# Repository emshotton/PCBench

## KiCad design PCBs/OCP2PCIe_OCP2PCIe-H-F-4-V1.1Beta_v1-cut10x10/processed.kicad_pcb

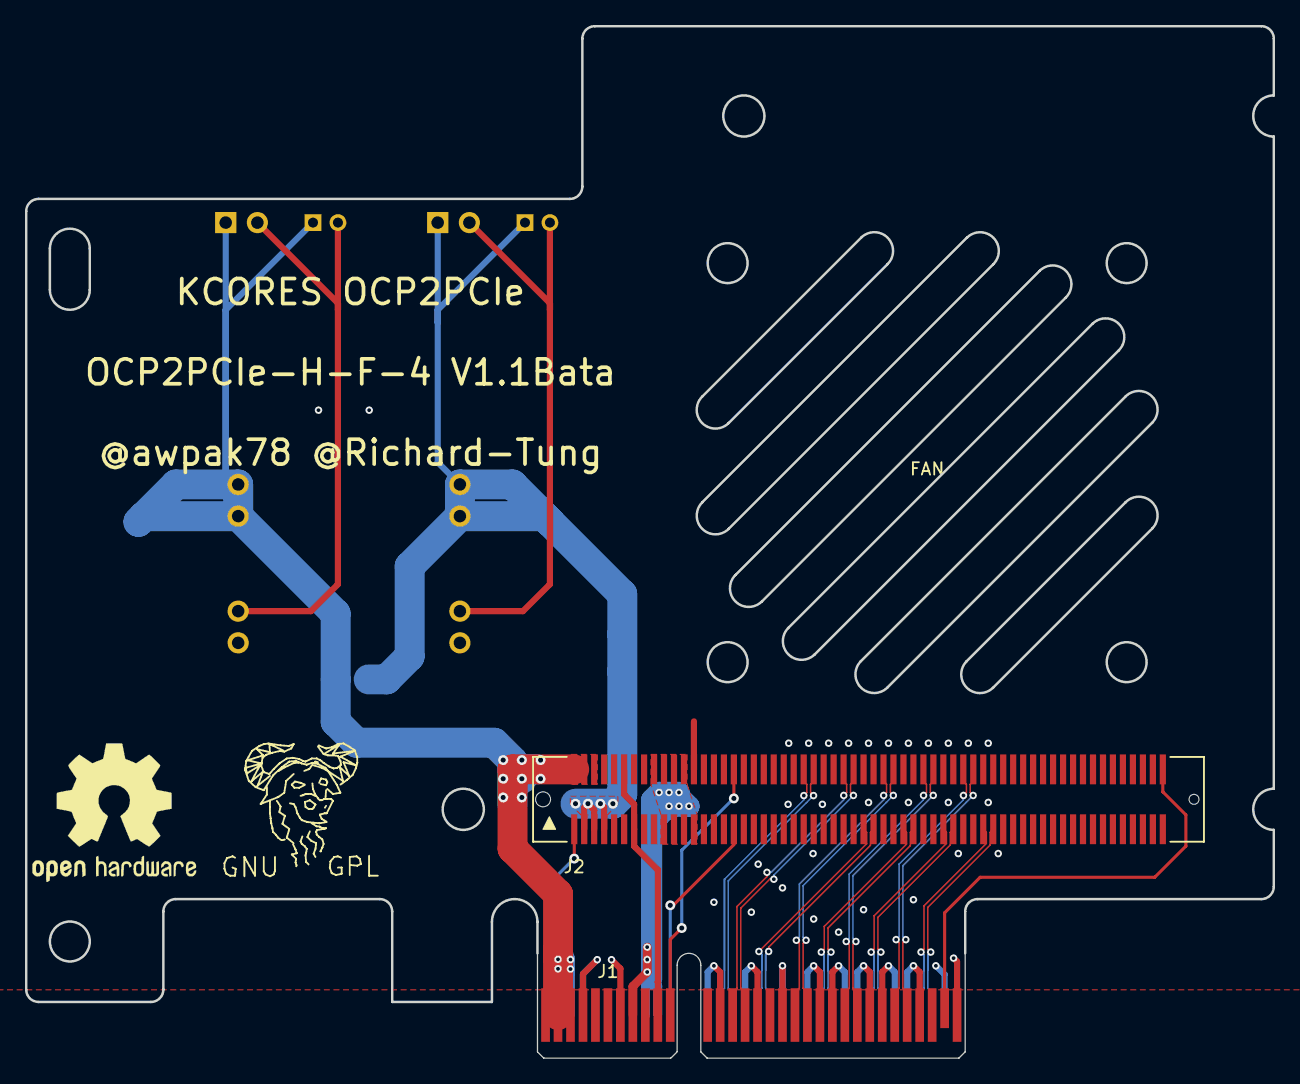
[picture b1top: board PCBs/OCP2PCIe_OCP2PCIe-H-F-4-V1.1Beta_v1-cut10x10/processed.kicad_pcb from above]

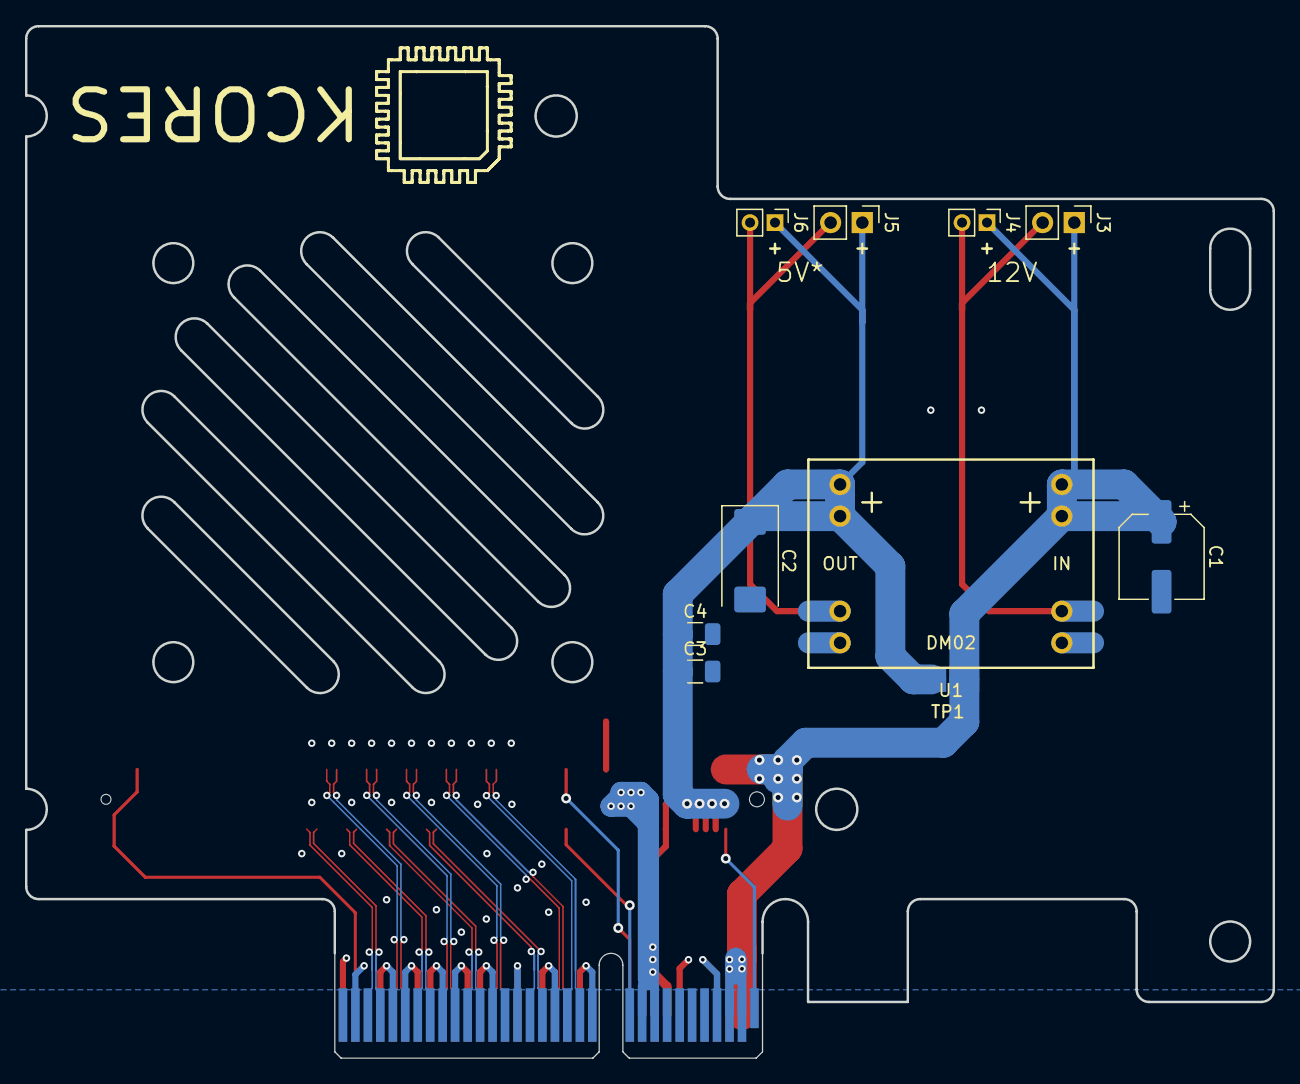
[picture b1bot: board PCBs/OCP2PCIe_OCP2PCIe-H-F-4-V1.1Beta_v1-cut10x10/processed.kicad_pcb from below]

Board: 2 copper layers, 100.1 x 82.8 mm, 13 parts (10 on the bottom side), 27 nets.

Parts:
C1: C; CP_Elec_6.3x5.4
C2: C; CP_EIA-7343-31_Kemet-D
C3, C4: C; C_1206_3216Metric
FAN: Fan_4010
J1: PCI Express x4; BUS_PCIexpress_x4
J2: Conn_02x40_Top_Bottom; FCI_61082_12xxxxLF
J3, J5: Conn_01x02; PinHeader_1x02_P2.54mm_Vertical
J4, J6: Conn_01x02; PinHeader_1x02_P2.00mm_Vertical
TP1: TestPoint_2Pole; TestPlot
U1: DM02

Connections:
3V3AUX: J1.B10, J2.7, J2.66
+3V3: J1.A9, J1.A10, J1.B8, J2.10, J2.11, J2.12, J2.13, J2.69, J2.70, J2.71, J2.72
+12V: C1.1, J1.A2, J1.A3, J1.B1, J1.B2, J1.B3, J2.61, J2.62, J2.63, J3.1, J4.1, TP1.1, U1.4
GND: C1.2, C2.2, C3.2, C4.2, J1.A4, J1.A12, J1.A15, J1.A18, J1.A20, J1.A23, J1.A24, J1.A27, J1.A28, J1.A31, J1.B4, J1.B7, J1.B13, J1.B16, J1.B18, J1.B21, J1.B22, J1.B25, J1.B26, J1.B29, J1.B32, J2.5, J2.6, J2.8, J2.9, J2.20, J2.21, J2.24, J2.25, J2.28, J2.29, J2.32, J2.33, J2.36, J2.37, J2.40, J2.41, J2.44, J2.45, J2.48, J2.49, J2.52, J2.53, J2.56, J2.57, J2.60, J2.64, J2.65, J2.67, J2.68, J2.73, J2.79, J2.82, J2.83, J2.86, J2.87, J2.90, J2.91, J2.94, J2.95, J2.98, J2.99, J2.102, J2.103, J2.106, J2.107, J2.110, J2.111, J2.114, J2.115, J2.118, J2.119, J3.2, J4.2, J5.2, J6.2, U1.2, U1.3
HSI0_N: J1.A17, J2.31
HSI0_P: J1.A16, J2.30
HSI1_N: J1.A22, J2.35
HSI1_P: J1.A21, J2.34
HSI2_N: J1.A26, J2.39
HSI2_P: J1.A25, J2.38
HSI3_N: J1.A30, J2.43
HSI3_P: J1.A29, J2.42
HSO0_N: J1.B15, J2.89
HSO0_P: J1.B14, J2.88
HSO1_N: J1.B20, J2.93
HSO1_P: J1.B19, J2.92
HSO2_N: J1.B24, J2.97
HSO2_P: J1.B23, J2.96
HSO3_N: J1.B28, J2.101
HSO3_P: J1.B27, J2.100
P5V_AUX: C2.1, C3.1, C4.1, J2.2, J2.3, J2.4, J5.1, J6.1, TP1.2, U1.1
PERST: J1.A11, J2.17
PRSNT1: J1.A1, J2.1
PRSNT2: J1.B31, J2.120
REFCLK+: J1.A13, J2.84
REFCLK-: J1.A14, J2.85
WAKE: J1.B11, J2.77

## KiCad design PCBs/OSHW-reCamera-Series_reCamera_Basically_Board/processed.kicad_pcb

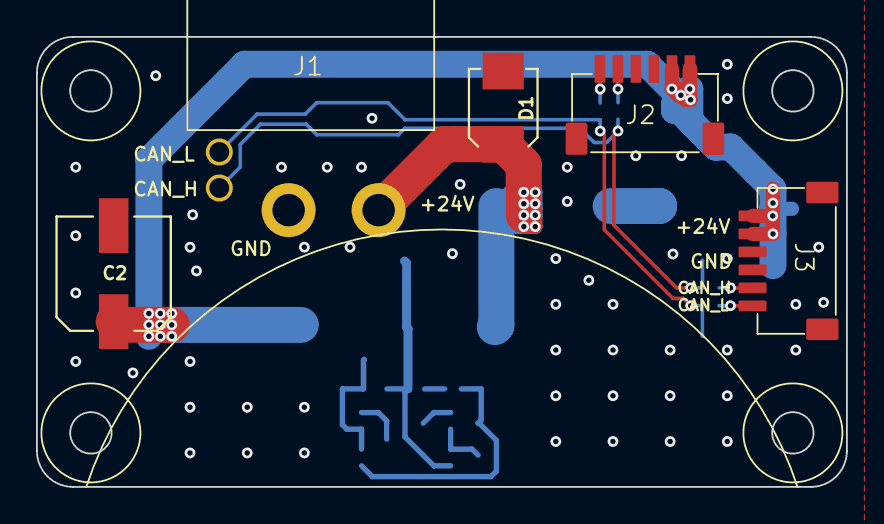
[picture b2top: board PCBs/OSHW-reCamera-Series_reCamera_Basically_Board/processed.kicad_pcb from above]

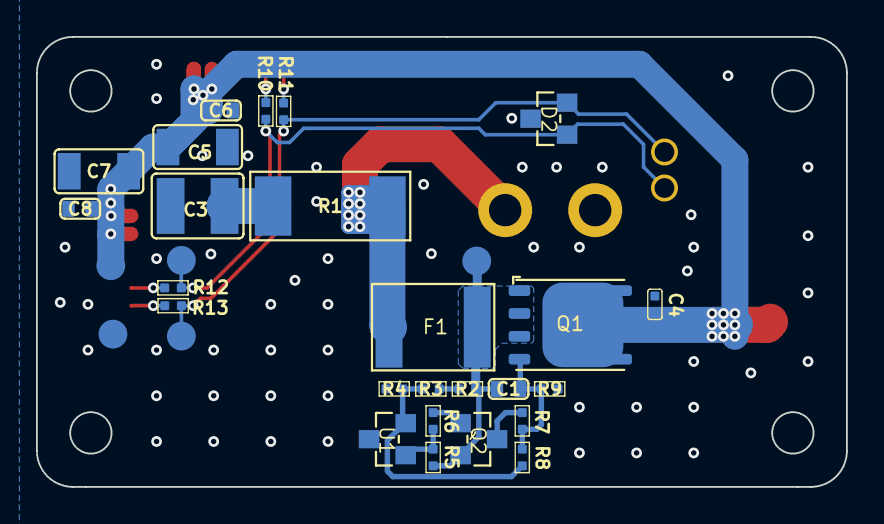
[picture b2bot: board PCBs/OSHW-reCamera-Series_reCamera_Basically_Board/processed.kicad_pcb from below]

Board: 2 copper layers, 45.0 x 25.0 mm, 35 parts (30 on the bottom side), 17 nets.

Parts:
C1, C6, C8: 100nF; C0603
C2: 47uF; ELECTRO-SMD-C-6MM
C3: 2.2uF; C1210
C4: 100pF; C0402
C5, C7: 10uF; C1206
D1: SMBJ24CA; DO-214AA_SMB
D2: SM05-7; SOT-23
F1: 2016L260/24MR; F2016
J1: ST-XT30(2+2)PW-M; XT30-2+2P-15.5x12.5x5.2mm
J2, J3: SM06B-SRSS-TB(LF)(SN); SMD-SH1.0-6P-90D
Q1: CJAC70P06; PG-TDSON-8-1.27-6X5X1MM
Q2: MMBT3906LT3G; SOT-23
R1: 2R; R2512
R2: 47K; R0402
R3, R10, R11, R12, R13: 0R; R0402
R4: 5.1K; R0402
R5: 20K; R0402
R6, R9: 100K; R0402
R7: 1K; R0402
R8: 1M; R0402
TP1, TP2, TP3, TP5, TP6: Test Point; TP-1.6MM-ROUND
U1: ATL431AIDBZR; SOT-23

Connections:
24V: C2.1, C4.1, C5.1, C6.1, C7.1, C8.1, J2.1, J2.2, J3.1, J3.2, Q1.5 (D1), Q1.6 (D2), Q1.7 (D3), Q1.8 (D4), Q1.9 (D5), TP2.1 (T)
24V_IN1: D1.2 (-), F1.1, J1.1 (+), R1.2
24V_IN2: C1.1, F1.2, Q1.1 (S1), Q1.2 (S2), Q1.3 (S3), Q2.2 (E), R2.2, R5.2, TP1.1 (T)
/03 Power/CAN_H: D2.1, J1.3 (H), R10.1, R12.1, TP5.1 (T)
/03 Power/CAN_L: D2.2, J1.4 (L), R11.1, R13.1, TP6.1 (T)
GND: C2.2, C3.2, C4.2, C5.2, C6.2, C7.2, C8.2, D1.1 (+), D2.3, J1.2 (-), J2.3, J2.4, J2.7, J2.8, J3.3, J3.4, J3.7, J3.8, R4.1, R9.1, TP3.1 (T), U1.3 (+)
unnamed: C3.1, R1.1
unnamed: J2.5, R10.2
unnamed: J2.6, R11.2
unnamed: J3.5, R12.2
unnamed: J3.6, R13.2
unnamed: C1.2, Q1.4 (G), R7.2, R8.2, R9.2
unnamed: Q2.1 (B), R6.1
unnamed: Q2.3 (C), R7.1
unnamed: R2.1, R3.2
unnamed: R5.1, R6.2, U1.1 (-)
unnamed: R3.1, R4.2, R8.1, U1.2 (Vref)

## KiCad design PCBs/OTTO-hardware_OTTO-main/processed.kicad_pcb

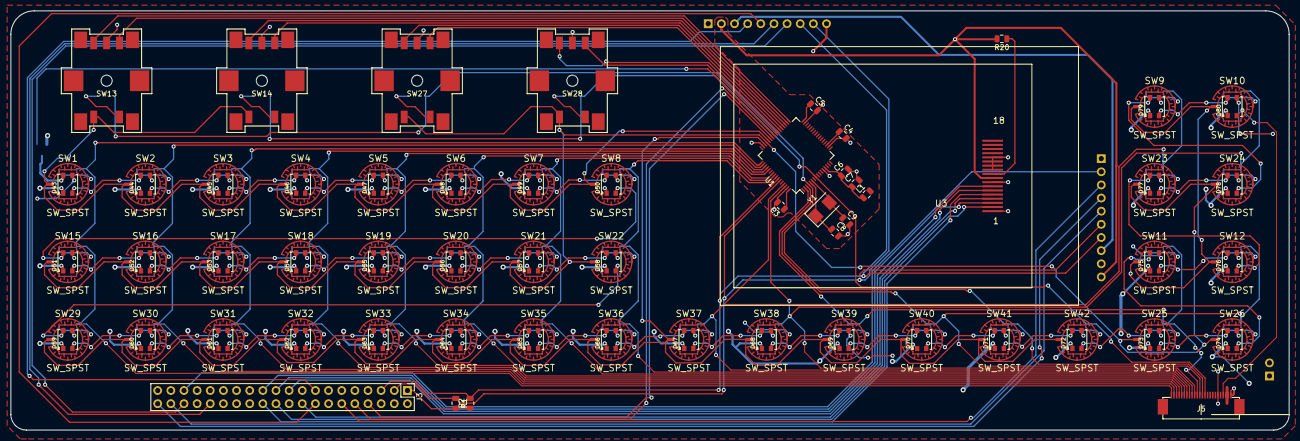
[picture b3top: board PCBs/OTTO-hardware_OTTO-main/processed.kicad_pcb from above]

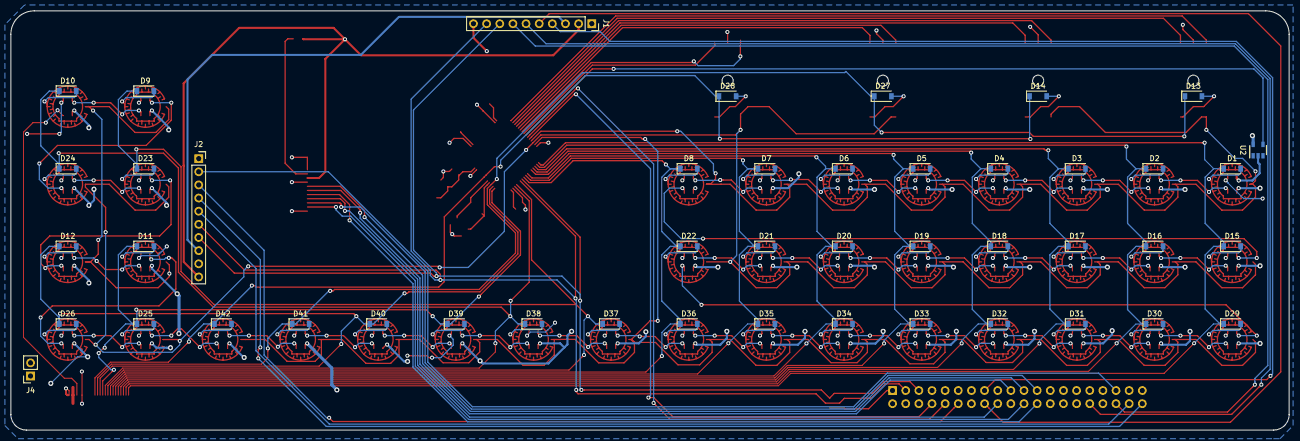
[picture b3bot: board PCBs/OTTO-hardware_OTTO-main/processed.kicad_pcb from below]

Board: 4 copper layers, 247.0 x 81.0 mm, 142 parts (46 on the bottom side), 133 nets.

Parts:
C3, C4, C5, C6: 1uf; C_0805_2012Metric
C7: 10nf; C_0805_2012Metric
C8, C9: 22pf; C_0805_2012Metric
D1, D2, D3, D4, D5, D6, D7, D8, D9, D10, D11, D12, D15, D16, D17, D18, D19, D20, D21, D22, D23, D24, D25, D26, D29, D30, D31, D32, D33, D34, D35, D36, D37, D38, D39, D40, D41, D42: D_ALT; D_SOD-123
D13, D14, D27, D28: 1N4148; D_SOD-123
D43, D44, D45, D46, D47, D48, D49, D50, D51, D52, D53, D54, D55, D56, D57, D58, D59, D60, D61, D62, D63, D64, D65, D66, D67, D68, D69, D70, D71, D72, D73, D74, D75, D76, D77, D78, D79, D80: WS2812B; WS2812B_3535
J1: POWER_BOARD; PinSocket_1x10_P2.54mm_Vertical
J2: AUDIO_BOARD; PinSocket_1x10_P2.54mm_Vertical
J3: Raspberry_Pi_2_3; PinHeader_2x20_P2.54mm_Vertical
J4: MICROPHONE; PinSocket_1x02_P2.54mm_Vertical
J5: Conn_01x24; JUSHUO_AFC07-S24FCC-00
L1: 30ohm; C_0805_2012Metric
R1, R2: 4.7K; R_0805_2012Metric
R20: 3.9; R_0805_2012Metric
SW1, SW2, SW3, SW4, SW5, SW6, SW7, SW8, SW9, SW10, SW11, SW12, SW15, SW16, SW17, SW18, SW19, SW20, SW21, SW22, SW23, SW24, SW25, SW26, SW29, SW30, SW31, SW32, SW33, SW34, SW35, SW36, SW37, SW38, SW39, SW40, SW41, SW42: SW_SPST; SILICONE_BUTTON_10MM_4X4WIDE
SW13, SW14, SW27, SW28: Rotary_Encoder_Switch; PEC11S-929K-S0015
U1: STM32F103RETx; LQFP-64_10x10mm_P0.5mm
U2: 74AHCT1G125; SOT-23-5
U3: ILI9341; ILI_DISPLAY
Y1: 8mhz; Crystal_SMD_5032-2Pin_5.0x3.2mm

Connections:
3V3: C3.1, C4.1, C5.1, J1.2, J2.10, L1.2, R20.2, U1.19, U1.32, U1.48, U1.64, U3.9
5V: D43.1, D44.1, D45.1, D46.1, D47.1, D48.1, D49.1, D50.1, D51.1, D52.1, D53.1, D54.1, D55.1, D56.1, D57.1, D58.1, D59.1, D60.1, D61.1, D62.1, D63.1, D64.1, D65.1, D66.1, D67.1, D68.1, D69.1, D70.1, D71.1, D72.1, D73.1, D74.1, D75.1, D76.1, D77.1, D78.1, D79.1, D80.1, J1.3, J2.8, J3.2, J5.22, J5.23, U2.5
BCLK: J2.3, J3.12
CE0: J3.24, U3.5
CHG_OUT: J1.7, J3.36
COL1: D1.1, D15.1, D29.1, J5.1, U1.49
COL2: D2.1, D16.1, D30.1, J5.2, U1.50
COL3: D3.1, D17.1, D31.1, J5.3, U1.51
COL4: D4.1, D18.1, D32.1, J5.4, U1.52
COL5: D5.1, D19.1, D33.1, J5.5, U1.53
COL6: D6.1, D20.1, D34.1, J5.6, U1.55
COL7: D7.1, D21.1, D35.1, J5.7, U1.56
COL8: D8.1, D22.1, D36.1, J5.8, U1.57
COL9: D9.1, D23.1, D37.1, J5.9, U1.61
COL10: D10.1, D24.1, D38.1, J5.10, U1.62
COL11: D11.1, D25.1, D39.1, J5.11, U1.2
COL12: D12.1, D26.1, D40.1, J5.12, U1.3
COL13: D13.1, D27.1, D41.1, J5.13, U1.4
COL14: D14.1, D28.1, D42.1, J5.14, U1.8
DOK_OUT: J1.6, J3.32
DOUT1: D52.2, D53.4
DOUT2: D66.2, D67.4
ENC1_A: SW13.A, U1.34
ENC1_B: SW13.B, U1.33
ENC2_A: SW14.A, U1.36
ENC2_B: SW14.B, U1.35
ENC3_A: SW27.A, U1.38
ENC3_B: SW27.B, U1.37
ENC4_A: SW28.A, U1.40
ENC4_B: SW28.B, U1.39
GND: C3.2, C4.2, C5.2, C6.2, C7.2, C8.2, C9.2, D43.3, D44.3, D45.3, D46.3, D47.3, D48.3, D49.3, D50.3, D51.3, D52.3, D53.3, D54.3, D55.3, D56.3, D57.3, D58.3, D59.3, D60.3, D61.3, D62.3, D63.3, D64.3, D65.3, D66.3, D67.3, D68.3, D69.3, D70.3, D71.3, D72.3, D73.3, D74.3, D75.3, D76.3, D77.3, D78.3, D79.3, D80.3, J1.1, J1.10, J2.1, J2.9, J3.6, J3.9, J3.14, J3.20, J3.25, J3.30, J3.34, J3.39, J5.19, J5.24, SW13.C, SW14.C, SW27.C, SW28.C, U1.12, U1.18, U1.31, U1.47, U1.63, U2.1, U2.3, U3.1, U3.8, U3.11, U3.12, U3.13, U3.14
GPIO24: J3.18, U3.4
GPIO25: J3.22, U3.2
I2S_RX: J2.4, J3.40
I2S_TX: J2.5, J3.38
KBLED: D80.2, J5.21
LEDIN: U1.41, U2.4
LR_CLK: J2.2, J3.35
MISO_0: J3.21, U3.7
MOSI_0: J3.19, U3.6
unnamed: C6.1, C7.1, L1.1, U1.13
unnamed: D1.2, SW1.2
unnamed: D2.2, SW2.2
unnamed: D3.2, SW3.2
unnamed: D4.2, SW4.2
unnamed: D5.2, SW5.2
unnamed: D6.2, SW6.2
unnamed: D7.2, SW7.2
unnamed: D8.2, SW8.2
unnamed: D9.2, SW9.2
unnamed: D10.2, SW10.2
unnamed: D11.2, SW11.2
unnamed: D12.2, SW12.2
unnamed: D13.2, SW13.S1
unnamed: D14.2, SW14.S1
unnamed: D15.2, SW15.2
unnamed: D16.2, SW16.2
unnamed: D17.2, SW17.2
unnamed: D18.2, SW18.2
unnamed: D19.2, SW19.2
unnamed: D20.2, SW20.2
unnamed: D21.2, SW21.2
unnamed: D22.2, SW22.2
unnamed: D23.2, SW23.2
unnamed: D24.2, SW24.2
unnamed: D25.2, SW25.2
unnamed: D26.2, SW26.2
unnamed: D27.2, SW27.S1
unnamed: D28.2, SW28.S1
unnamed: D29.2, SW29.2
unnamed: D30.2, SW30.2
unnamed: D31.2, SW31.2
unnamed: D32.2, SW32.2
unnamed: D33.2, SW33.2
unnamed: D34.2, SW34.2
unnamed: D35.2, SW35.2
unnamed: D36.2, SW36.2
unnamed: D37.2, SW37.2
unnamed: D38.2, SW38.2
unnamed: D39.2, SW39.2
unnamed: D40.2, SW40.2
unnamed: D41.2, SW41.2
unnamed: D42.2, SW42.2
unnamed: D43.2, D44.4
unnamed: D43.4, U2.2
unnamed: D44.2, D45.4
unnamed: D45.2, D46.4
unnamed: D46.2, D47.4
unnamed: D47.2, D48.4
unnamed: D48.2, D49.4
unnamed: D49.2, D50.4
unnamed: D50.2, D51.4
unnamed: D51.2, D52.4
unnamed: D53.2, D54.4
unnamed: D54.2, D55.4
unnamed: D55.2, D56.4
unnamed: D56.2, D57.4
unnamed: D57.2, D58.4
unnamed: D58.2, D59.4
unnamed: D59.2, D60.4
unnamed: D60.2, D61.4
unnamed: D61.2, D62.4
unnamed: D62.2, D63.4
unnamed: D63.2, D64.4
unnamed: D64.2, D65.4
unnamed: D65.2, D66.4
unnamed: D67.2, D68.4
unnamed: D68.2, D69.4
unnamed: D69.2, D70.4
unnamed: D70.2, D71.4
unnamed: D71.2, D72.4
unnamed: D72.2, D73.4
unnamed: D73.2, D74.4
unnamed: D74.2, D75.4
unnamed: D75.2, D76.4
unnamed: D76.2, D77.4
unnamed: D77.2, D78.4
unnamed: D78.2, D79.4
unnamed: D79.2, D80.4
unnamed: J3.1, R1.2, R2.1
unnamed: R20.1, U3.10
OSC_IN: C8.1, U1.5, Y1.1
OSC_OUT: C9.1, U1.6, Y1.2
OUT_PIN: J1.4, J3.15
ROW1: SW1.1, SW2.1, SW3.1, SW4.1, SW5.1, SW6.1, SW7.1, SW8.1, SW9.1, SW10.1, SW11.1, SW12.1, SW13.S2, SW14.S2, U1.44
ROW2: SW15.1, SW16.1, SW17.1, SW18.1, SW19.1, SW20.1, SW21.1, SW22.1, SW23.1, SW24.1, SW25.1, SW26.1, SW27.S2, SW28.S2, U1.45
ROW3: SW29.1, SW30.1, SW31.1, SW32.1, SW33.1, SW34.1, SW35.1, SW36.1, SW37.1, SW38.1, SW39.1, SW40.1, SW41.1, SW42.1, U1.46
SCL: J1.8, J2.7, J3.5, R2.2, U1.58
SCLK_0: J3.23, U3.3
SDA: J1.9, J2.6, J3.3, R1.1, U1.59
SENSE_PIN: J1.5, J3.16
UART_RXD: J3.10, U1.42
UART_TXD: J3.8, U1.43

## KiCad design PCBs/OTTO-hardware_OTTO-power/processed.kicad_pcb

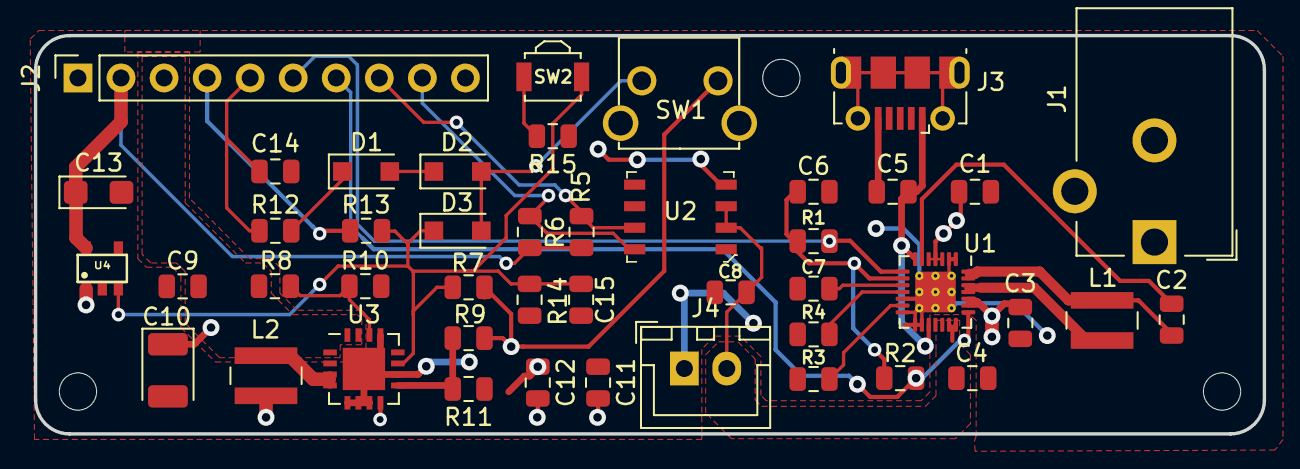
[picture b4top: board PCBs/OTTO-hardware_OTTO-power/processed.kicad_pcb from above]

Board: 2 copper layers, 72.5 x 23.5 mm, 45 parts (0 on the bottom side), 28 nets.

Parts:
C1, C6, C9: 2.2uf; C_0805_2012Metric
C2: 1uf; C_0805_2012Metric
C3, C4, C11: 10uf; C_0805_2012Metric
C5: 4.7uf; C_0805_2012Metric
C7: 0.15uf; C_0805_2012Metric
C8, C12, C14: 0.1uf; C_0805_2012Metric
C10: 100uf; CP_EIA-3528-21_Kemet-B
C13: 10uf; CP_EIA-3216-18_Kemet-A
C15: 100uf; C_0805_2012Metric
D1, D2, D3: IN4001; D_SOD-123F
J1: Barrel_Jack; BarrelJack_CUI_PJ-102AH_Horizontal
J2: Conn_01x10; PinSocket_1x10_P2.54mm_Vertical
J3: USB_B_Micro; USB_Micro-B_Molex-105017-0001
J4: battery; JST_XH_B02B-XH-A_1x02_P2.50mm_Vertical
L1: 3.3uH; L_Wuerth_MAPI-4020
L2: 6.8uH; L_Wuerth_MAPI-4020
R1, R2, R5, R6, R14: 100K; R_0805_2012Metric
R3: 1.2K; R_0805_2012Metric
R4: 3K; R_0805_2012Metric
R7, R10: 200K; R_0805_2012Metric
R8, R9: 1.87M; R_0805_2012Metric
R11: 340K; R_0805_2012Metric
R12, R13: 10K; R_0805_2012Metric
R15: 1K; R_0805_2012Metric
SW1: SW_Push; SKHHLVA010
SW2: SW_reset; SW_SPST_B3U-3000P
U1: MAX8903A; QFN-28-1EP_4x4mm_P0.4mm_EP2.4x2.4mm_ThermalVias
U2: MAX17048; TDFN-8-1EP
U3: TPS61090; QFN-16-1EP_4x4mm_P0.65mm_EP2.5x2.5mm
U4: XC6210; SOT25

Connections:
3V3: C13.1, J2.2, R5.2, R6.2, U4.5
5V: C9.2, C10.1, J2.3, R8.2, U3.1, U3.15, U3.16
BATT+: C4.2, C8.2, J4.2, U1.20, U1.21, U2.2, U2.3
CHG_OUT: J2.7, R2.1, U1.22
DC: C1.1, J1.1, U1.3, U1.4, U1.5
DOK_OUT: J2.6, R1.1, U1.8
EN_PI: C15.1, D3.1, R7.1, R13.1, R14.2, SW2.2, U3.11, U4.3
GNDA: C1.2, C3.1, C4.1, C5.1, C6.1, C7.1, C8.1, C9.1, C10.2, C11.1, C12.1, C13.2, C14.2, C15.2, J1.2, J2.1, J2.10, J3.5, J4.1, R3.1, R4.1, R10.1, R11.1, R14.1, R15.1, U1.1, U1.2, U1.12, U1.14, U1.15, U1.16, U1.29, U2.1, U2.4, U2.6, U3.5, U3.6, U3.7, U3.10, U3.13, U3.17, U4.2
unnamed: C2.1, U1.6
unnamed: C2.2, L1.2, U1.27, U1.28
unnamed: C7.2, U1.10
unnamed: D1.1, R12.1
unnamed: D1.2, D2.1
unnamed: D2.2, D3.2, SW1.2
unnamed: L1.1, U1.25, U1.26
unnamed: L2.1, U3.3, U3.4
unnamed: R3.2, U1.13
unnamed: R4.2, U1.11
unnamed: R8.1, R10.2, U3.14
unnamed: R9.1, R11.2, U3.9
unnamed: R15.2, SW2.1
OUT_PIN: J2.4, R13.2
SCL: J2.8, R5.1, U2.7
SDA: J2.9, R6.1, U2.8
SENSE_PIN: C14.1, J2.5, R12.2
SYS: C3.2, C11.2, C12.2, L2.2, R7.2, R9.2, SW1.1, U1.23, U1.24, U3.8, U4.1
USB: C5.2, J3.1, U1.7, U1.17
VL: C6.2, R1.2, R2.2, U1.9

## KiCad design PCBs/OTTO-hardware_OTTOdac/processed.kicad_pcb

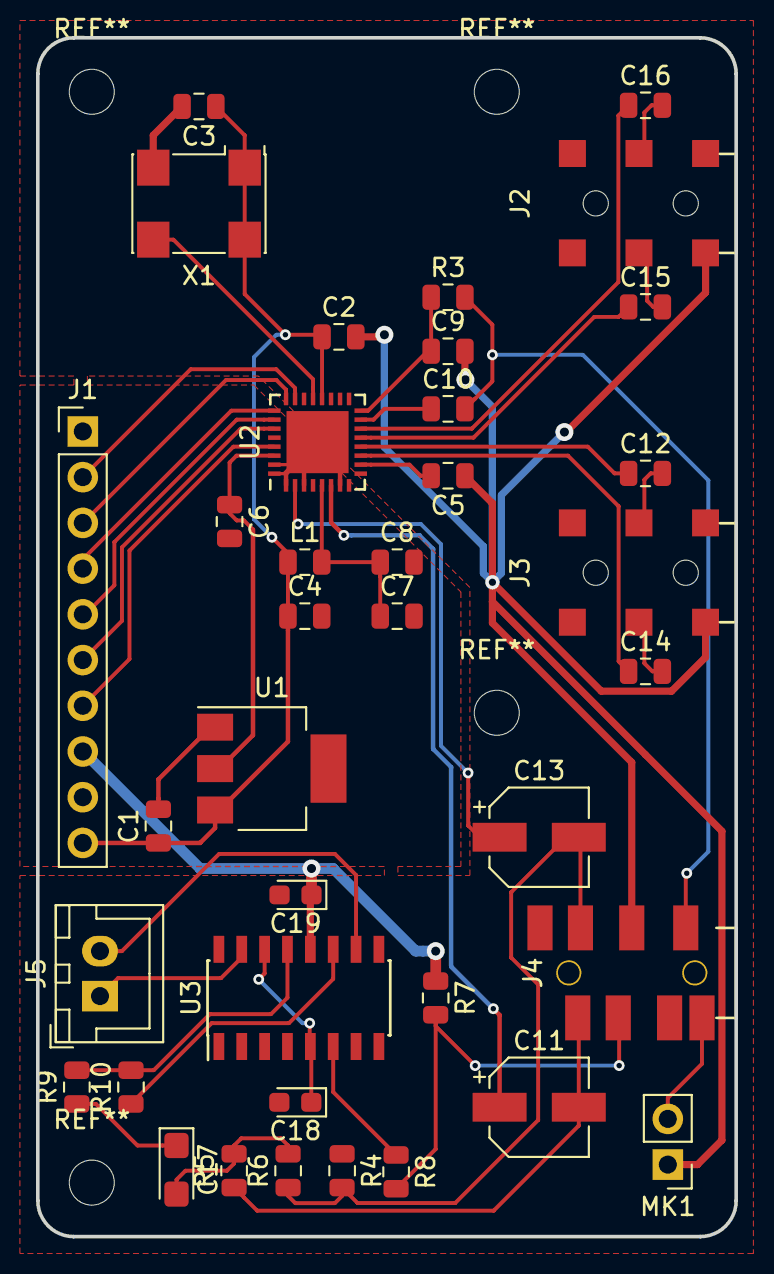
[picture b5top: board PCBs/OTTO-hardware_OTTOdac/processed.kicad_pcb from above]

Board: 2 copper layers, 38.8 x 66.6 mm, 38 parts (0 on the bottom side), 39 nets.

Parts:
C1, C6, C7, C9, C12, C14, C15, C16: 2.2uf; C_0805_2012Metric
C2, C3, C4, C5, C8, C10: 0.1uf; C_0805_2012Metric
C11, C13: 220uf; CP_Elec_5x4.5
C17: 1uf; CP_EIA-3216-18_Kemet-A
C18, C19: 0.1uf; CP_EIA-2012-12_Kemet-R
J1: Conn_01x10; PinHeader_1x10_P2.54mm_Vertical
J2: Audio_IN; PJ-237-6A
J3: Audio_OUT; PJ-237-6A
J4: SJ1-42536-SMT; PJ-393-7A
J5: Speaker; JST_XH_B02B-XH-A_1x02_P2.50mm_Vertical
L1: 600; Fuse_0805_2012Metric
MK1: Microphone; PinHeader_1x02_P2.54mm_Vertical
R3: 2.2K; R_0805_2012Metric
R4, R5, R6: 1K; R_0805_2012Metric
R7, R8: 100K; R_0805_2012Metric
R9, R10: 10K; R_0805_2012Metric
U1: AMS1117-3.3; SOT-223-3_TabPin2
U2: SGTL5000; QFN-32-NXP-SGTL5000
U3: LM4860; SOIC-16_3.9x9.9mm_P1.27mm
X1: XO32; Oscillator_SMD_Abracon_ASV-4Pin_7.0x5.1mm

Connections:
+3V3: C1.1, C2.1, C3.1, C4.1, J1.10, L1.1, U1.3, U2.20, X1.1, X1.4
+5V: C19.1, J1.8, R7.1, U3.12
GNDREF: C1.2, C2.2, C3.2, C4.2, C5.1, C6.2, C7.2, C8.2, C9.2, C18.2, C19.2, J1.1, J1.9, J2.1, J3.1, J4.4, MK1.1, R4.1, U1.1, U2.1, U2.3, U2.7, U2.31, U2.32, U2.33, U3.1, U3.4, U3.9, X1.2
HPL: C11.2, J4.2, R5.1
HPR: C13.2, J4.3, R4.2, R6.1
MIC: C10.2, J4.1, R3.2
unnamed: C5.2, U2.10
unnamed: C6.1, U1.2, U2.30
unnamed: C7.1, C8.1, L1.2, U2.5
unnamed: C9.1, R3.1, U2.16
unnamed: C10.1, U2.15
unnamed: C11.1, U2.6
unnamed: C12.1, U2.12
unnamed: C12.2, J3.2
unnamed: C13.1, U2.2
unnamed: C14.1, U2.11
unnamed: C14.2, J3.3
unnamed: C15.1, U2.13
unnamed: C15.2, J2.3
unnamed: C16.1, U2.14
unnamed: C16.2, J2.2
unnamed: C17.1, R9.1
unnamed: C17.2, R5.2, R6.2
unnamed: C18.1, U3.5, U3.14
unnamed: J4.6, R7.2, R8.2
unnamed: J4.8, MK1.2
unnamed: J5.1, U3.15
unnamed: J5.2, U3.10
unnamed: R8.1, U3.6
unnamed: R10.1, U3.11
unnamed: R9.2, R10.2, U3.13
unnamed: U2.21, X1.3
unnamed: U3.2, U3.3
PIN3: J1.6, U2.27
PIN5: J1.7, U2.29
PIN12: J1.3, U2.24
PIN35: J1.2, U2.23
PIN38: J1.5, U2.26
PIN40: J1.4, U2.25

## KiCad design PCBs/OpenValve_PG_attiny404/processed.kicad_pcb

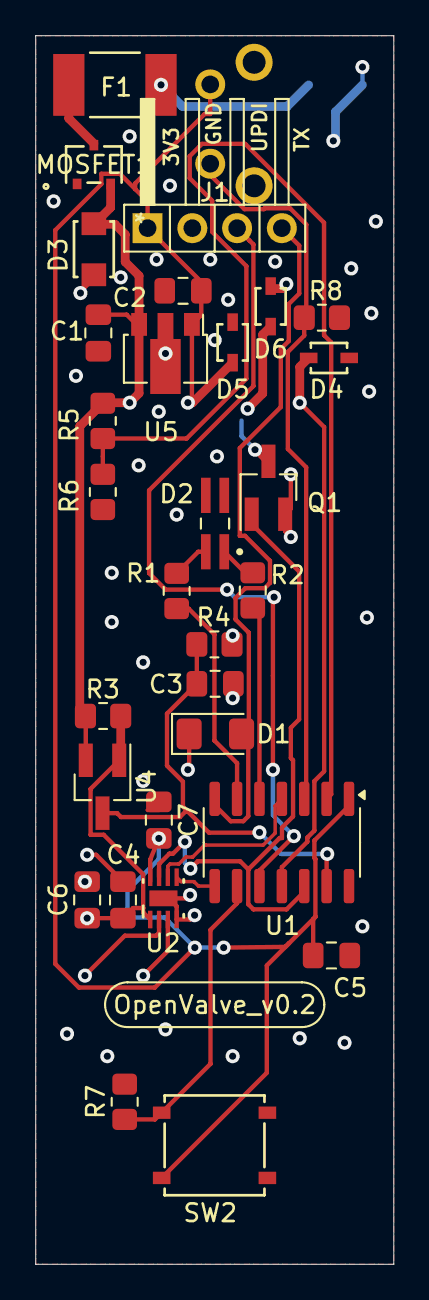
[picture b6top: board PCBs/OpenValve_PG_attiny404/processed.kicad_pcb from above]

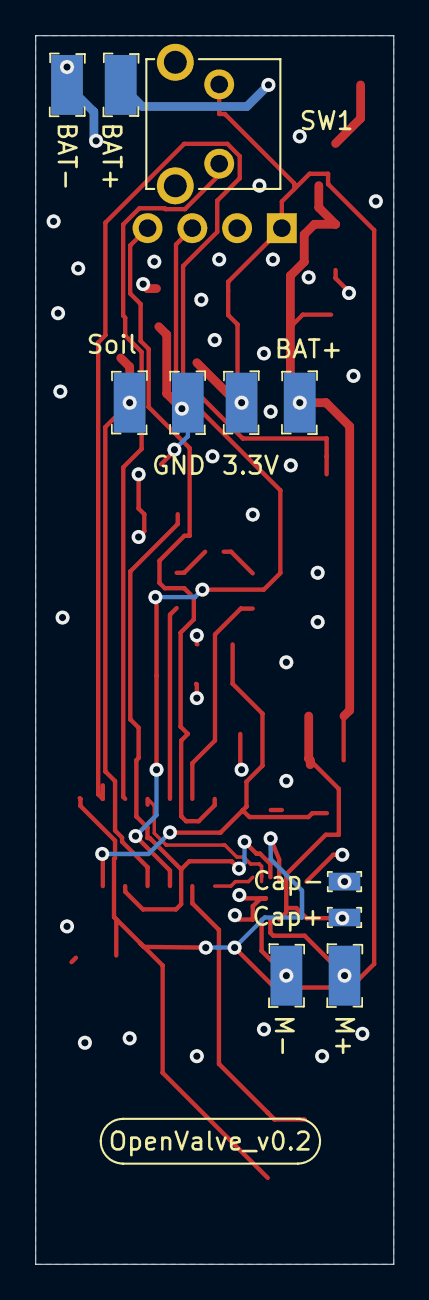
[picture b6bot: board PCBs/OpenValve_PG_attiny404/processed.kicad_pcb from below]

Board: 2 copper layers, 20.3 x 69.7 mm, 41 parts (11 on the bottom side), 23 nets.

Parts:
C1, C2, C5: 1uF; C_0805_2012Metric_Pad1.18x1.45mm_HandSolder
C3, C6, C7: 100nF; C_0805_2012Metric_Pad1.18x1.45mm_HandSolder
C4: 10uF; C_0805_2012Metric_Pad1.18x1.45mm_HandSolder
D1: APTD3216QBC/D; LED_1206_3216Metric_Pad1.42x1.75mm_HandSolder
D2: XZMDKVG55W-8; LED_XZMDKVG55W-8
D3: SMF13A; SMFSeries_LTF
D4, D5, D6: ESDA041-1JY; CR_041-1JY_STM
F1: 0ZCG0075FF2C
J1: 0022232041; PinHeader_1x04_P2.54mm_Horizontal_spezial
J2, J3, J4, J5, J6, J7, J8, J9: Conn_01x01_Male; PROBE_PAD_1206
J10: Cap +; PROBE_PAD_0603
J11: Cap -; PROBE_PAD_0603
MOSFET1: SSM3J338R_LF; SOT-23F_TOS
Q1: 2N7002K-AU_R1_000A2; SOT-23_Handsoldering
R1: 62 Ohm; R_0805_2012Metric_Pad1.20x1.40mm_HandSolder
R2: 100 Ohm; R_0805_2012Metric_Pad1.20x1.40mm_HandSolder
R3: 0.5 Ohm; R_0805_2012Metric_Pad1.20x1.40mm_HandSolder
R4: 665 Ohm; R_0805_2012Metric_Pad1.20x1.40mm_HandSolder
R5: 2M; R_0805_2012Metric_Pad1.20x1.40mm_HandSolder
R6: 1M; R_0805_2012Metric_Pad1.20x1.40mm_HandSolder
R7: 10k; R_0805_2012Metric_Pad1.20x1.40mm_HandSolder
R8: 220k; R_0805_2012Metric_Pad1.20x1.40mm_HandSolder
SW1: SW_Push; 1825027-2
SW2: PTS526 SM15 SMTR2 LFS; PTS526SK15SMTR2 LFS-M
U1: ATtiny804-SS; SOIC-14_3.9x8.7mm_P1.27mm
U2: DRV8837DSGR; DRV8837DSGR_NV
U4: ZXCT1009F; SOT-23_Handsoldering_ZXCT1009F
U5: AP7370-33Y-13; SOT-89-3

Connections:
+3V3: C2.2, C5.2, C7.2, D5.1 (C), J1.1, J4.1, SW1.2, SW2.2, U1.1 (VCC), U2.8 (VCC), U5.1 (Vout)
+BATT: C1.2, D3.1 (C), J9.1, MOSFET1.2, R3.2, R5.1, U4.2 (Vs+), U5.3 (Vin)
/BatterySensing: R5.2, R6.1, U1.2 (PA4)
/CurrentSensing: C3.2, R4.2, U1.13 (PA3), U4.1 (Iout)
/Hall: R7.1, SW2.4, U1.9 (PB0)
/LED_G: R1.2, U1.6 (PB3)
/LED_R: R2.2, U1.5 (PA7)
/Motor+: U1.8 (PB1), U2.5 (IN2)
/Motor-: U1.4 (PA6), U2.6 (IN1)
/MotorStop: R8.2, SW1.1, U1.3 (PA5)
/SoilSensorOn: Q1.1 (G), U1.12 (PA2), U2.7 (SLEEP_N)
/Soilmoisture: D4.1 (C), J6.1, U1.11 (PA1)
/UART_TX: D1.2 (A), J1.4, U1.7 (PB2)
/UPDI: J1.3, U1.10 (~RESET/PA0)
GND: C1.1, C2.1, C3.1, C4.1, C5.1, C6.1, C7.1, D1.1 (K), D2.2, D2.4, D3.2 (A), D4.2 (A), D5.2 (A), D6.2 (A), J1.2, J2.1, J11.1, MOSFET1.1, Q1.2 (S), R4.1, R6.2, R7.2, R8.1, U1.14 (GND), U2.4 (GND), U2.9 (PAD), U5.2 (GND)
unnamed: D2.1, R2.1
unnamed: D2.3, R1.1
unnamed: D6.1 (C), J5.1, Q1.3 (D)
unnamed: F1.2, MOSFET1.3
unnamed: F1.1, J3.1
unnamed: J7.1, U2.3 (OUT2)
unnamed: J8.1, U2.2 (OUT1)
unnamed: C4.2, C6.2, J10.1, R3.1, U2.1 (VM), U4.3 (Vs-)

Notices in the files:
parts and their libraries:
Copyright 2021 Accelerated Designs. All rights reserved.
